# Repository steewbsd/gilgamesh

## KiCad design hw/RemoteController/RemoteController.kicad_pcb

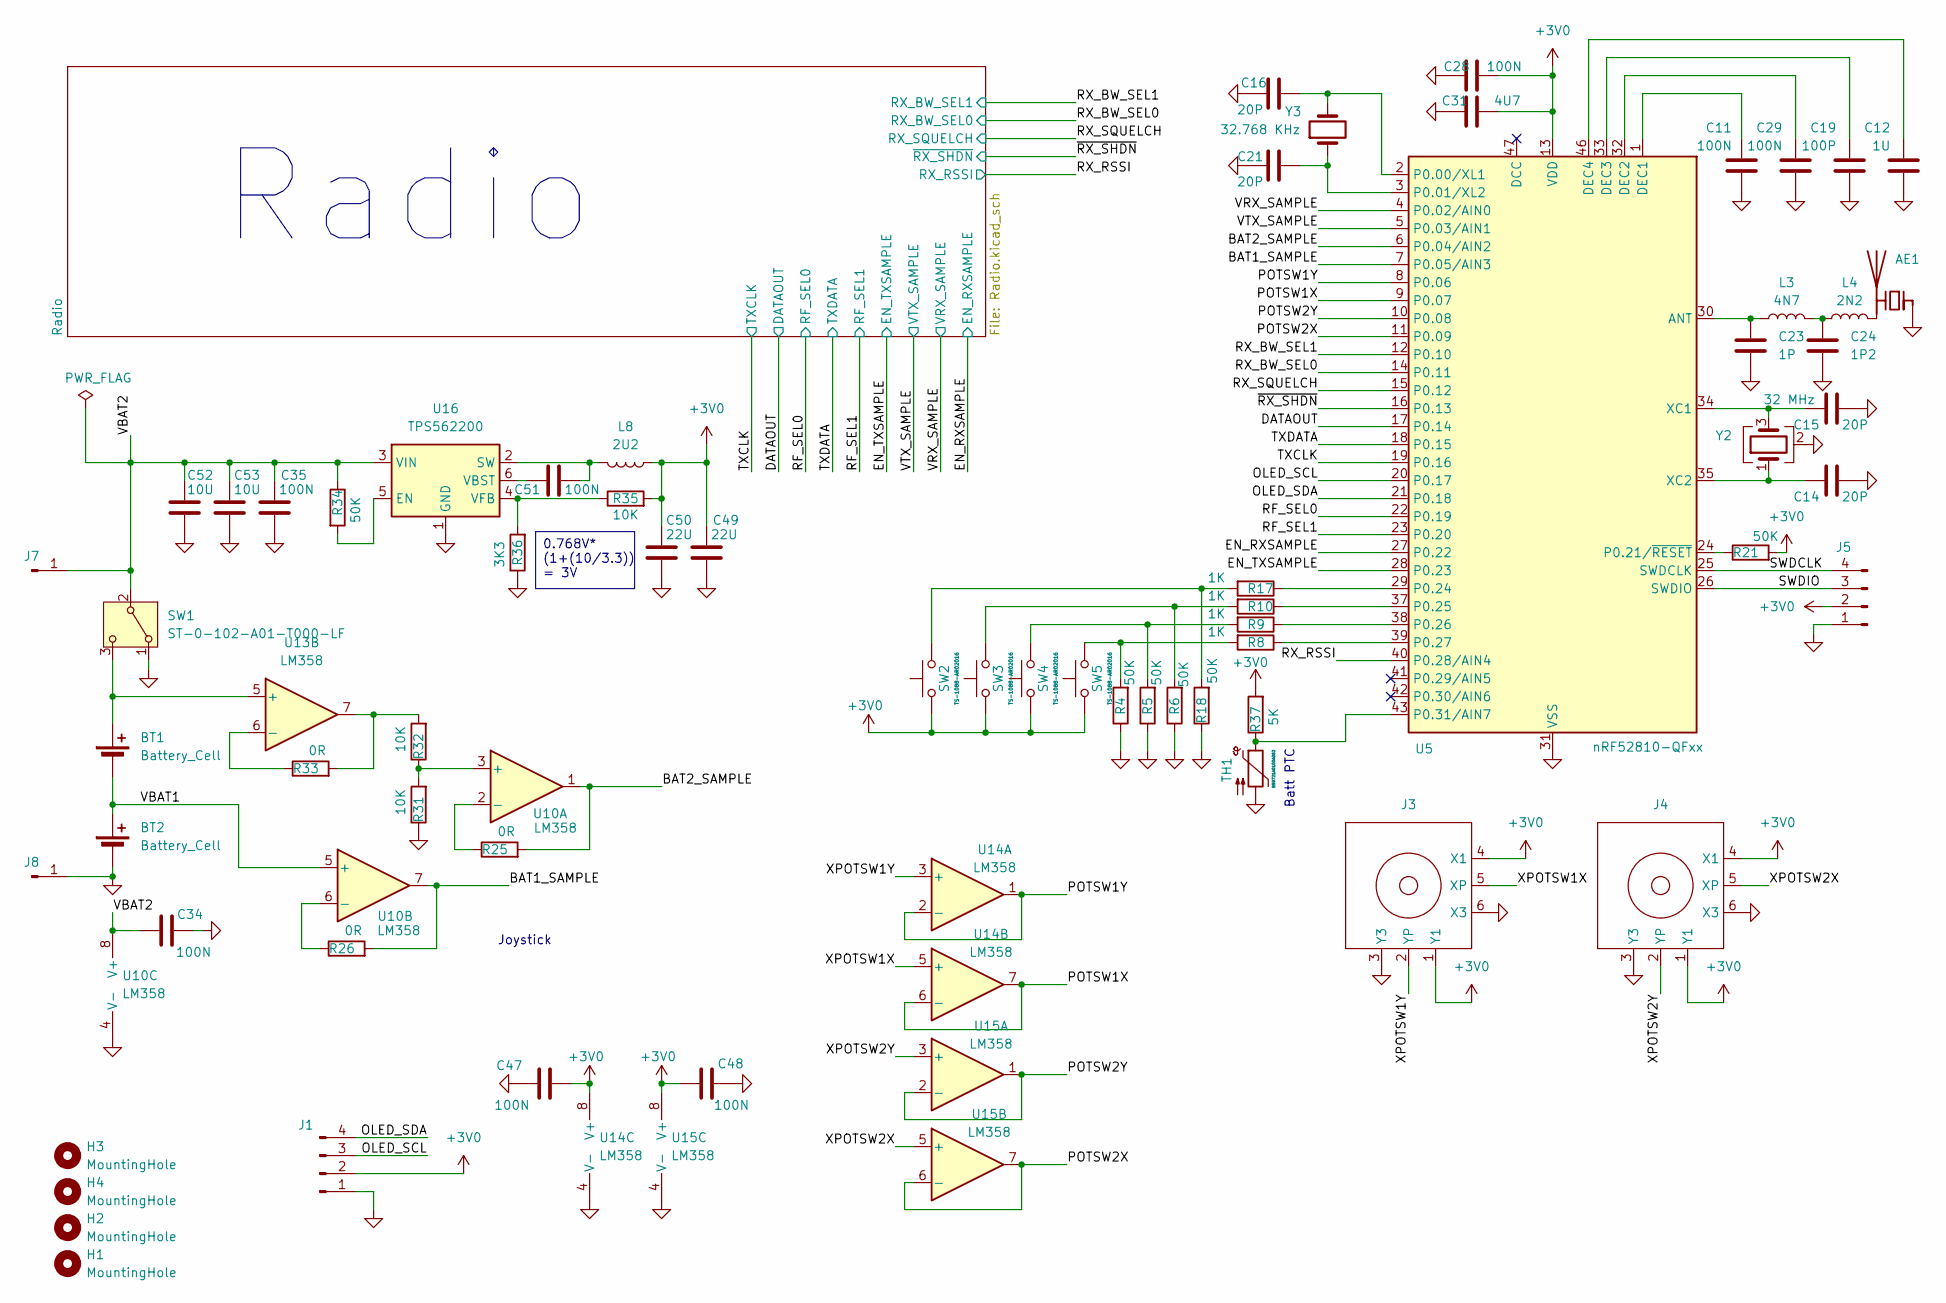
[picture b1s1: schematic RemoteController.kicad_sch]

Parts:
AE1: Antenna_Chip; L_1206_3216Metric_Pad1.22x1.90mm_HandSolder
BT1, BT2: Battery_Cell; BH-AAA-B5BA021
C11, C28, C29, C34, C35, C47, C48, C51: 100N; C_0402_1005Metric_Pad0.74x0.62mm_HandSolder
C12: 1U; C_0402_1005Metric_Pad0.74x0.62mm_HandSolder
C14, C15, C16, C21: 20P; C_0402_1005Metric_Pad0.74x0.62mm_HandSolder
C19: 100P; C_0402_1005Metric_Pad0.74x0.62mm_HandSolder
C23: 1P; C_0402_1005Metric_Pad0.74x0.62mm_HandSolder
C24: 1P2; C_0402_1005Metric_Pad0.74x0.62mm_HandSolder
C31: 4U7; C_0402_1005Metric_Pad0.74x0.62mm_HandSolder
C49, C50: 22U; C_0402_1005Metric_Pad0.74x0.62mm_HandSolder
C52, C53: 10U; C_0402_1005Metric_Pad0.74x0.62mm_HandSolder
H1, H2, H3, H4: MountingHole; MountingHole_2.2mm_M2
J1: Conn_01x04_Pin; PinSocket_1x04_P2.54mm_Horizontal
J3, J4: YG16-FL7.8-B10Ka(80)-R
J5: Conn_01x04_Pin; JST_PH_B4B-PH-K_1x04_P2.00mm_Vertical
J7, J8: Conn_01x01_Pin; PinSocket_1x01_P2.54mm_Vertical
L3: 4N7; L_0603_1608Metric_Pad1.05x0.95mm_HandSolder
L4: 2N2; L_0603_1608Metric_Pad1.05x0.95mm_HandSolder
L8: 2U2; L_0603_1608Metric_Pad1.05x0.95mm_HandSolder
R4, R5, R6, R18, R21, R34: 50K; R_0402_1005Metric_Pad0.72x0.64mm_HandSolder
R8, R9, R10, R17: 1K; R_0402_1005Metric_Pad0.72x0.64mm_HandSolder
R25, R26, R33: 0R; R_0402_1005Metric_Pad0.72x0.64mm_HandSolder
R31, R32, R35: 10K; R_0402_1005Metric_Pad0.72x0.64mm_HandSolder
R36: 3K3; R_0402_1005Metric_Pad0.72x0.64mm_HandSolder
R37: 5K; R_0402_1005Metric_Pad0.72x0.64mm_HandSolder
SW1: ST-0-102-A01-T000-LF; SW_Slide-03_Wuerth-WS-SLTV_10x2.5x6.4_P2.54mm
SW2, SW3, SW4, SW5: TS-1088-AR02016; SW_SPST_TS-1088-xR020
TH1: B59721A0100A062; R_0805_2012Metric_Pad1.20x1.40mm_HandSolder
U5: nRF52810-QFxx; QFN-48-1EP_6x6mm_P0.4mm_EP4.2x4.2mm
U10, U13, U14, U15: LM358; SOIC-8_3.9x4.9mm_P1.27mm
U16: TPS562200; SOT-23-6
Y2: 32 MHz; Crystal_SMD_3225-4Pin_3.2x2.5mm_HandSoldering
Y3: 32.768 KHz; Crystal_SMD_3215-2Pin_3.2x1.5mm

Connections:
+3V0: C28.1, C31.1, C47.2, C48.1, C49.1, C50.1, J1.2, J3.1 (Y1), J3.4 (X1), J4.1 (Y1), J4.4 (X1), J5.2, L8.2, R21.2, R35.2, R37.2, SW2.1, SW3.1, SW4.1, SW5.1, U5.13 (VDD), U5.36 (VDD), U5.48 (VDD), U14.8 (V+), U15.8 (V+); also elsewhere on the board
/BAT1_SAMPLE: R26.2, U5.7 (P0.05/AIN3), U10.7
/BAT2_SAMPLE: R25.2, U5.6 (P0.04/AIN2), U10.1
/DATAOUT: U5.17 (P0.14); also elsewhere on the board
/EN_RXSAMPLE: U5.27 (P0.22); also elsewhere on the board
/EN_TXSAMPLE: U5.28 (P0.23); also elsewhere on the board
/OLED_SCL: J1.3, U5.20 (P0.17)
/OLED_SDA: J1.4, U5.21 (P0.18)
/POTSW1X: U5.9 (P0.07), U14.6 (-), U14.7
/POTSW1Y: U5.8 (P0.06), U14.1, U14.2 (-)
/POTSW2X: U5.11 (P0.09), U15.6 (-), U15.7
/POTSW2Y: U5.10 (P0.08), U15.1, U15.2 (-)
/RF_SEL0: U5.22 (P0.19); also elsewhere on the board
/RF_SEL1: U5.23 (P0.20); also elsewhere on the board
/RX_BW_SEL0: U5.14 (P0.11); also elsewhere on the board
/RX_BW_SEL1: U5.12 (P0.10); also elsewhere on the board
/RX_RSSI: U5.40 (P0.28/AIN4); also elsewhere on the board
/RX_SQUELCH: U5.15 (P0.12); also elsewhere on the board
/SWDCLK: J5.4, U5.25 (SWDCLK)
/SWDIO: J5.3, U5.26 (SWDIO)
/TXCLK: U5.19 (P0.16); also elsewhere on the board
/TXDATA: U5.18 (P0.15); also elsewhere on the board
/VBAT1: BT1.2 (-), BT2.1 (+), U10.5 (+)
/VBAT2: C34.1, C35.1, C52.1, C53.1, J7.1 (Pin_1_1), R34.1, SW1.2 (B), U10.8 (V+), U16.3 (VIN)
/VRX_SAMPLE: U5.4 (P0.02/AIN0); also elsewhere on the board
/VTX_SAMPLE: U5.5 (P0.03/AIN1); also elsewhere on the board
/XPOTSW1X: J3.5 (XP), U14.5 (+)
/XPOTSW1Y: J3.2 (YP), U14.3 (+)
/XPOTSW2X: J4.5 (XP), U15.5 (+)
/XPOTSW2Y: J4.2 (YP), U15.3 (+)
/~RX_SHDN: U5.16 (P0.13); also elsewhere on the board
GND: AE1.1 (FEED), BT2.2 (-), C11.2, C12.2, C14.2, C15.2, C16.2, C19.2, C21.2, C23.2, C24.2, C28.2, C29.2, C31.2, C34.2, C35.2, C47.1, C48.2, C49.2, C50.2, C52.2, C53.2, J1.1, J3.3 (Y3), J3.6 (X3), J4.3 (Y3), J4.6 (X3), J5.1, J8.1 (Pin_1_1), R4.1, R5.1, R6.1, R18.1, R31.1, R36.1, SW1.1 (A), TH1.2, U5.31 (VSS), U5.45 (VSS), U5.49 (VSS), U10.4 (V-), U14.4 (V-), U15.4 (V-), U16.1 (GND), Y2.2 (G), Y2.4 (G); also elsewhere on the board
unnamed: AE1.2 (PCB_Trace), L4.2
unnamed: BT1.1 (+), SW1.3 (C), U13.5 (+)
unnamed: C24.1, L3.2, L4.1
unnamed: R4.2, R8.2, SW5.2
unnamed: R5.2, R9.2, SW4.2
unnamed: R6.2, R10.2, SW3.2
unnamed: R17.2, R18.2, SW2.2
unnamed: R32.2, R33.2, U13.7
unnamed: C23.1, L3.1, U5.30 (ANT)
unnamed: C11.1, U5.1 (DEC1)
unnamed: C29.1, U5.32 (DEC2)
unnamed: C19.1, U5.33 (DEC3)
unnamed: C12.1, U5.46 (DEC4)
unnamed: C16.1, U5.2 (P0.00/XL1), Y3.2
unnamed: C21.1, U5.3 (P0.01/XL2), Y3.1
unnamed: R21.1, U5.24 (P0.21/~RESET)
unnamed: R17.1, U5.29 (P0.24)
unnamed: R10.1, U5.37 (P0.25)
unnamed: R9.1, U5.38 (P0.26)
unnamed: R8.1, U5.39 (P0.27)
unnamed: R37.1, TH1.1, U5.43 (P0.31/AIN7)
unnamed: C15.1, U5.34 (XC1), Y2.3
unnamed: C14.1, U5.35 (XC2), Y2.1
unnamed: R31.2, R32.1, U10.3 (+)
unnamed: R25.1, U10.2 (-)
unnamed: R26.1, U10.6 (-)
unnamed: R33.1, U13.6 (-)
unnamed: R34.2, U16.5 (EN)
unnamed: C51.2, L8.1, U16.2 (SW)
unnamed: C51.1, U16.6 (VBST)
unnamed: R35.1, R36.2, U16.4 (VFB)

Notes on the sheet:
Batt PTC
Joystick
Radio
0.768V* (1+(10/3.3)) = 3V

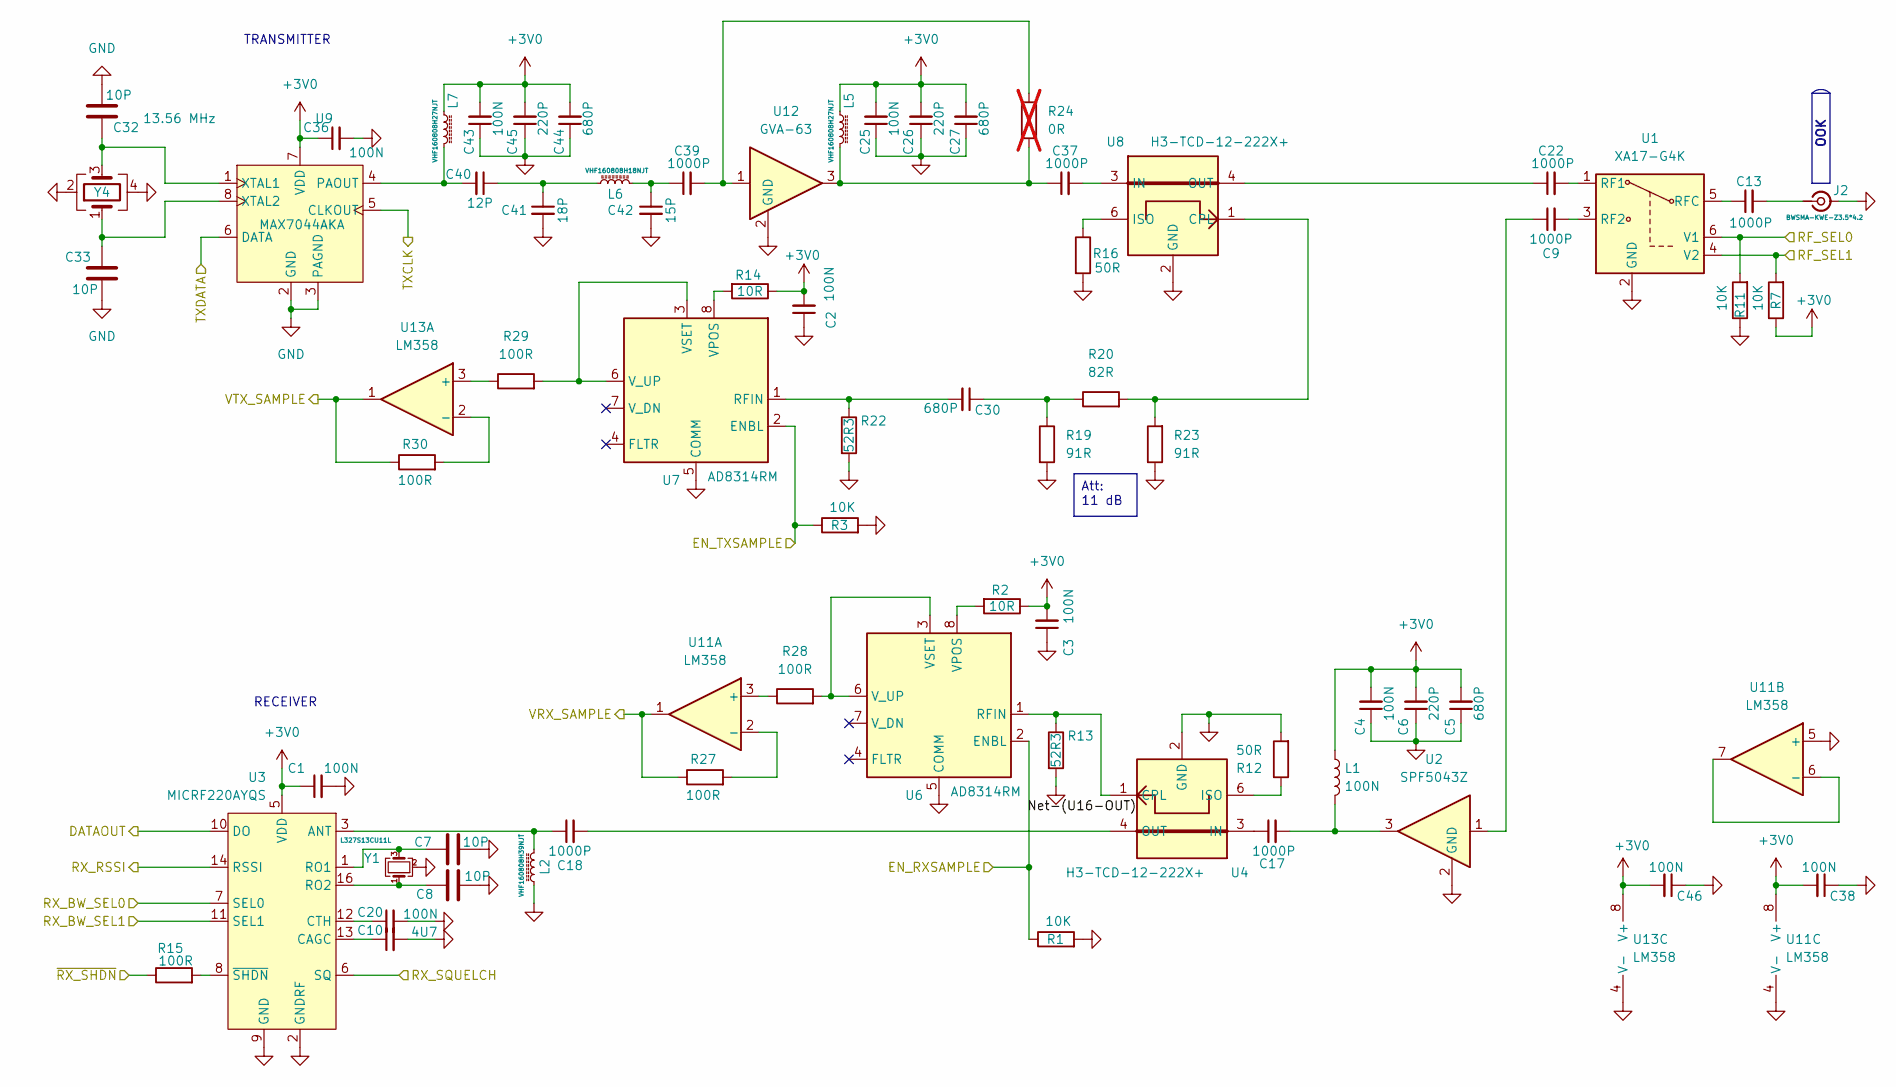
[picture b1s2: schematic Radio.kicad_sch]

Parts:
C1, C2, C3, C4, C20, C25, C36, C38, C43, C46: 100N; C_0402_1005Metric_Pad0.74x0.62mm_HandSolder
C5, C27, C30, C44: 680P; C_0402_1005Metric_Pad0.74x0.62mm_HandSolder
C6, C26, C45: 220P; C_0402_1005Metric_Pad0.74x0.62mm_HandSolder
C7, C8, C32, C33: 10P; C_0402_1005Metric_Pad0.74x0.62mm_HandSolder
C9, C13, C17, C18, C22, C37, C39: 1000P; C_0402_1005Metric_Pad0.74x0.62mm_HandSolder
C10: 4U7; C_0402_1005Metric_Pad0.74x0.62mm_HandSolder
C40: 12P; C_0402_1005Metric_Pad0.74x0.62mm_HandSolder
C41: 18P; C_0402_1005Metric_Pad0.74x0.62mm_HandSolder
C42: 15P; C_0402_1005Metric_Pad0.74x0.62mm_HandSolder
J2: BWSMA-KWE-Z3.5*4.2; SMA_BAT_Wireless_BWSMA-KWE-Z001
L1: 100N; L_0603_1608Metric_Pad1.05x0.95mm_HandSolder
L2: VHF160808H39NJT; L_0603_1608Metric_Pad1.05x0.95mm_HandSolder
L5, L7: 27N; L_0603_1608Metric_Pad1.05x0.95mm_HandSolder
L6: VHF160808H18NJT; L_0603_1608Metric_Pad1.05x0.95mm_HandSolder
R1, R3, R7, R11: 10K; R_0402_1005Metric_Pad0.72x0.64mm_HandSolder
R2, R14: 10R; R_0402_1005Metric_Pad0.72x0.64mm_HandSolder
R12, R16: 50R; R_0402_1005Metric_Pad0.72x0.64mm_HandSolder
R13, R22: 52R3; R_0402_1005Metric_Pad0.72x0.64mm_HandSolder
R15, R27, R28, R29, R30: 100R; R_0402_1005Metric_Pad0.72x0.64mm_HandSolder
R19, R23: 91R; R_0402_1005Metric_Pad0.72x0.64mm_HandSolder
R20: 82R; R_0402_1005Metric_Pad0.72x0.64mm_HandSolder
R24: 0R; R_0402_1005Metric_Pad0.72x0.64mm_HandSolder; not fitted
U1: XA17-G4K; SOT-363_SC-70-6
U2: SPF5043Z; SOT-343_SC-70-4
U3: MICRF220AYQS; QSOP-16_3.9x4.9mm_P0.635mm
U4, U8: H3-TCD-12-222X+; Mini-Circuits_DB1627
U6, U7: AD8314RM; MSOP-8_3x3mm_P0.65mm
U9: MAX7044AKA; TSOT-23-8_HandSoldering
U11, U13: LM358; SOIC-8_3.9x4.9mm_P1.27mm
U12: GVA-63; SOT-89-3_Handsoldering
Y1: L327S13CU11L; Crystal_SMD_3225-4Pin_3.2x2.5mm_HandSoldering
Y4: 13.56 MHz; Crystal_SMD_3225-4Pin_3.2x2.5mm_HandSoldering

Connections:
+3V0: C1.1, C2.2, C3.2, C4.2, C5.2, C6.2, C25.2, C26.2, C27.2, C36.1, C38.2, C43.2, C44.2, C45.2, C46.2, L1.1, L5.1, L7.1, R2.1, R7.1, R14.1, U3.5 (VDD), U9.7 (VDD), U11.8 (V+), U13.8 (V+); also elsewhere on the board
/DATAOUT: U3.10 (DO); also elsewhere on the board
/EN_RXSAMPLE: R1.1, U6.2 (ENBL); also elsewhere on the board
/EN_TXSAMPLE: R3.1, U7.2 (ENBL); also elsewhere on the board
/RF_SEL0: R11.2, U1.6 (V1); also elsewhere on the board
/RF_SEL1: R7.2, U1.4 (V2); also elsewhere on the board
/RX_BW_SEL0: U3.7 (SEL0); also elsewhere on the board
/RX_BW_SEL1: U3.11 (SEL1); also elsewhere on the board
/RX_RSSI: U3.14 (RSSI); also elsewhere on the board
/RX_SQUELCH: U3.6 (SQ); also elsewhere on the board
/TXCLK: U9.5 (CLKOUT); also elsewhere on the board
/TXDATA: U9.6 (DATA); also elsewhere on the board
/VRX_SAMPLE: R27.1, U11.1; also elsewhere on the board
/VTX_SAMPLE: R30.1, U13.1; also elsewhere on the board
/~RX_SHDN: R15.1; also elsewhere on the board
GND: C1.2, C2.1, C3.1, C4.1, C5.1, C6.1, C7.1, C8.1, C10.2, C20.2, C25.1, C26.1, C27.1, C32.2, C33.2, C36.2, C38.1, C41.2, C42.2, C43.1, C44.1, C45.1, C46.1, J2.2 (Ext), L2.1, R1.2, R3.2, R11.1, R12.2, R13.2, R16.2, R19.2, R22.2, R23.1, U1.2 (GND), U2.2 (GND), U2.4 (GND), U3.2 (GNDRF), U3.4 (GNDRF), U3.9 (GND), U4.2 (GND), U6.5 (COMM), U7.5 (COMM), U8.2 (GND), U9.2 (GND), U9.3 (PAGND), U11.4 (V-), U11.5 (+), U12.2 (GND_2), U13.4 (V-), Y1.2 (G), Y1.4 (G), Y4.2, Y4.4; also elsewhere on the board
unnamed: C9.1, U2.1
unnamed: C17.2, L1.2, U2.3
unnamed: C30.1, R19.1, R20.1
unnamed: C37.1, L5.2, R24.1, U12.3
unnamed: C39.1, C42.1, L6.2
unnamed: C39.2, R24.2, U12.1
unnamed: C40.1, C41.1, L6.1
unnamed: C13.2, J2.1 (In)
unnamed: C22.2, U1.1 (RF1)
unnamed: C9.2, U1.3 (RF2)
unnamed: C13.1, U1.5 (RFC)
unnamed: C18.1, L2.2, U3.3 (ANT)
unnamed: C10.1, U3.13 (CAGC)
unnamed: C20.1, U3.12 (CTH)
unnamed: C7.2, U3.1 (RO1), Y1.3
unnamed: C8.2, U3.16 (RO2), Y1.1
unnamed: R15.2, U3.8 (~SHDN)
unnamed: R13.1, U4.1 (CPL), U6.1 (RFIN)
unnamed: C17.1, U4.3 (IN)
unnamed: R12.1, U4.6 (ISO)
unnamed: C18.2, U4.4 (OUT)
unnamed: R2.2, U6.8 (VPOS)
unnamed: R28.2, U6.3 (VSET), U6.6 (V_UP)
unnamed: C30.2, R22.1, U7.1 (RFIN)
unnamed: R14.2, U7.8 (VPOS)
unnamed: R29.2, U7.3 (VSET), U7.6 (V_UP)
unnamed: R20.2, R23.2, U8.1 (CPL)
unnamed: C37.2, U8.3 (IN)
unnamed: R16.1, U8.6 (ISO)
unnamed: C22.1, U8.4 (OUT)
unnamed: C40.2, L7.2, U9.4 (PAOUT)
unnamed: C32.1, U9.1 (XTAL1), Y4.3
unnamed: C33.1, U9.8 (XTAL2), Y4.1
unnamed: R28.1, U11.3 (+)
unnamed: R27.2, U11.2 (-)
unnamed: U11.6 (-), U11.7
unnamed: R29.1, U13.3 (+)
unnamed: R30.2, U13.2 (-)

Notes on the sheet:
RECEIVER
TRANSMITTER
OOK
Att: 11 dB

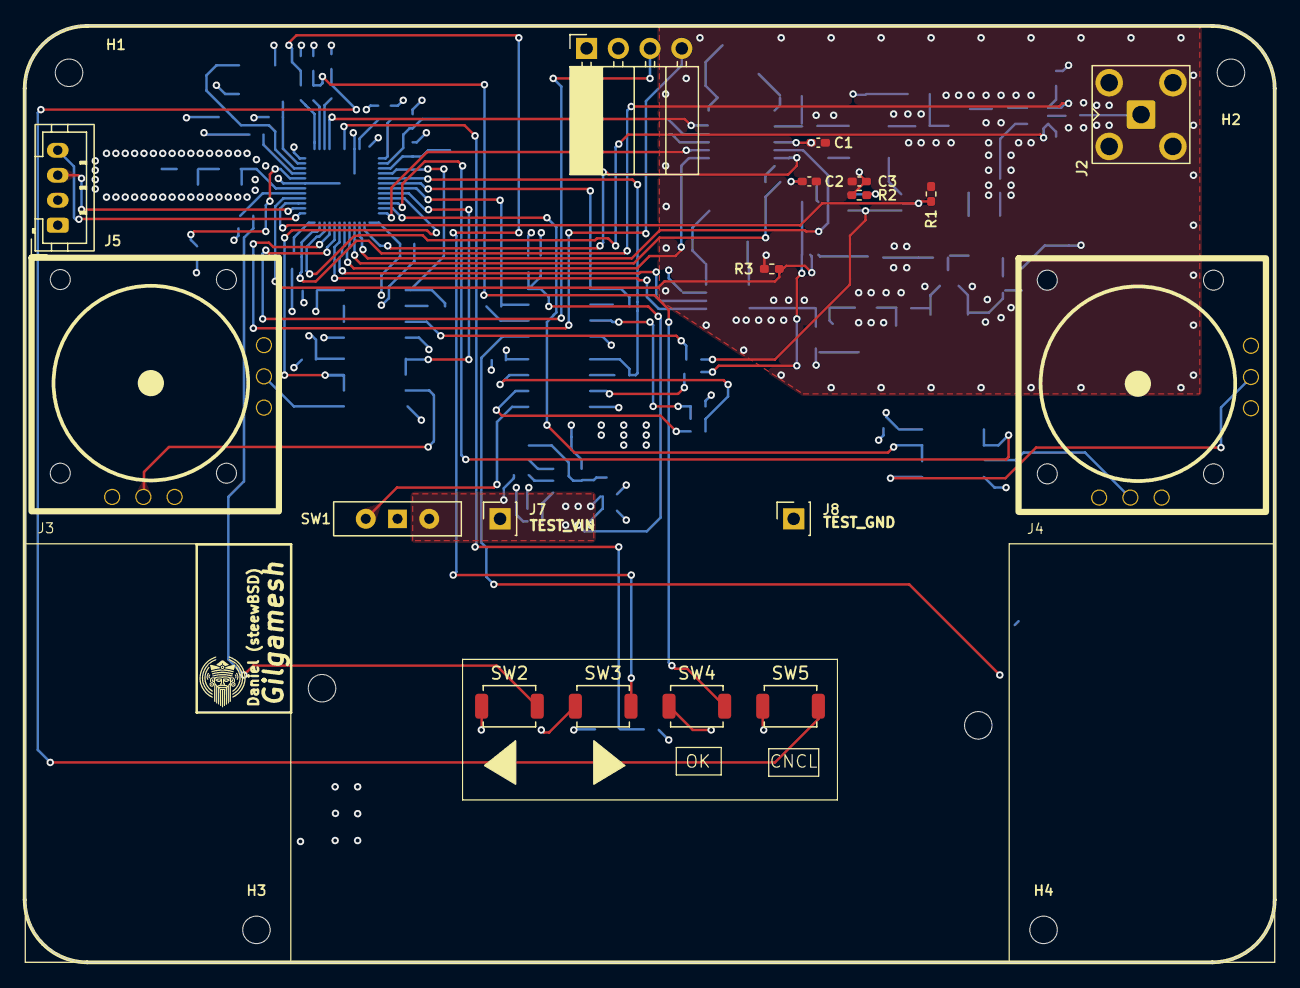
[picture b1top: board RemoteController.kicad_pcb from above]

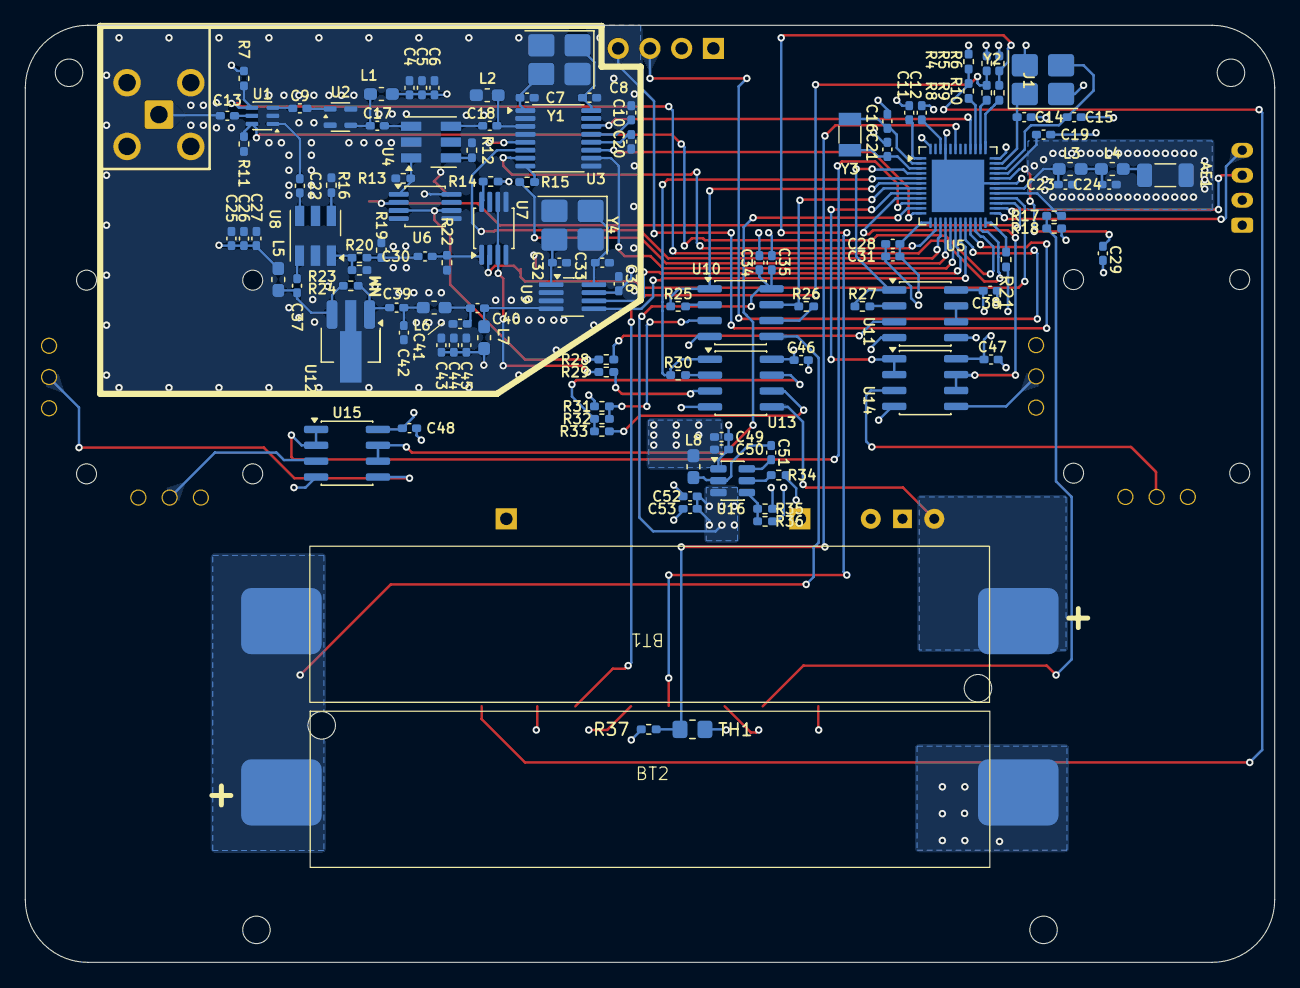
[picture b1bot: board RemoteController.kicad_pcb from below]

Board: 4 copper layers, 100.0 x 75.0 mm, 138 parts (116 on the bottom side), 101 nets.

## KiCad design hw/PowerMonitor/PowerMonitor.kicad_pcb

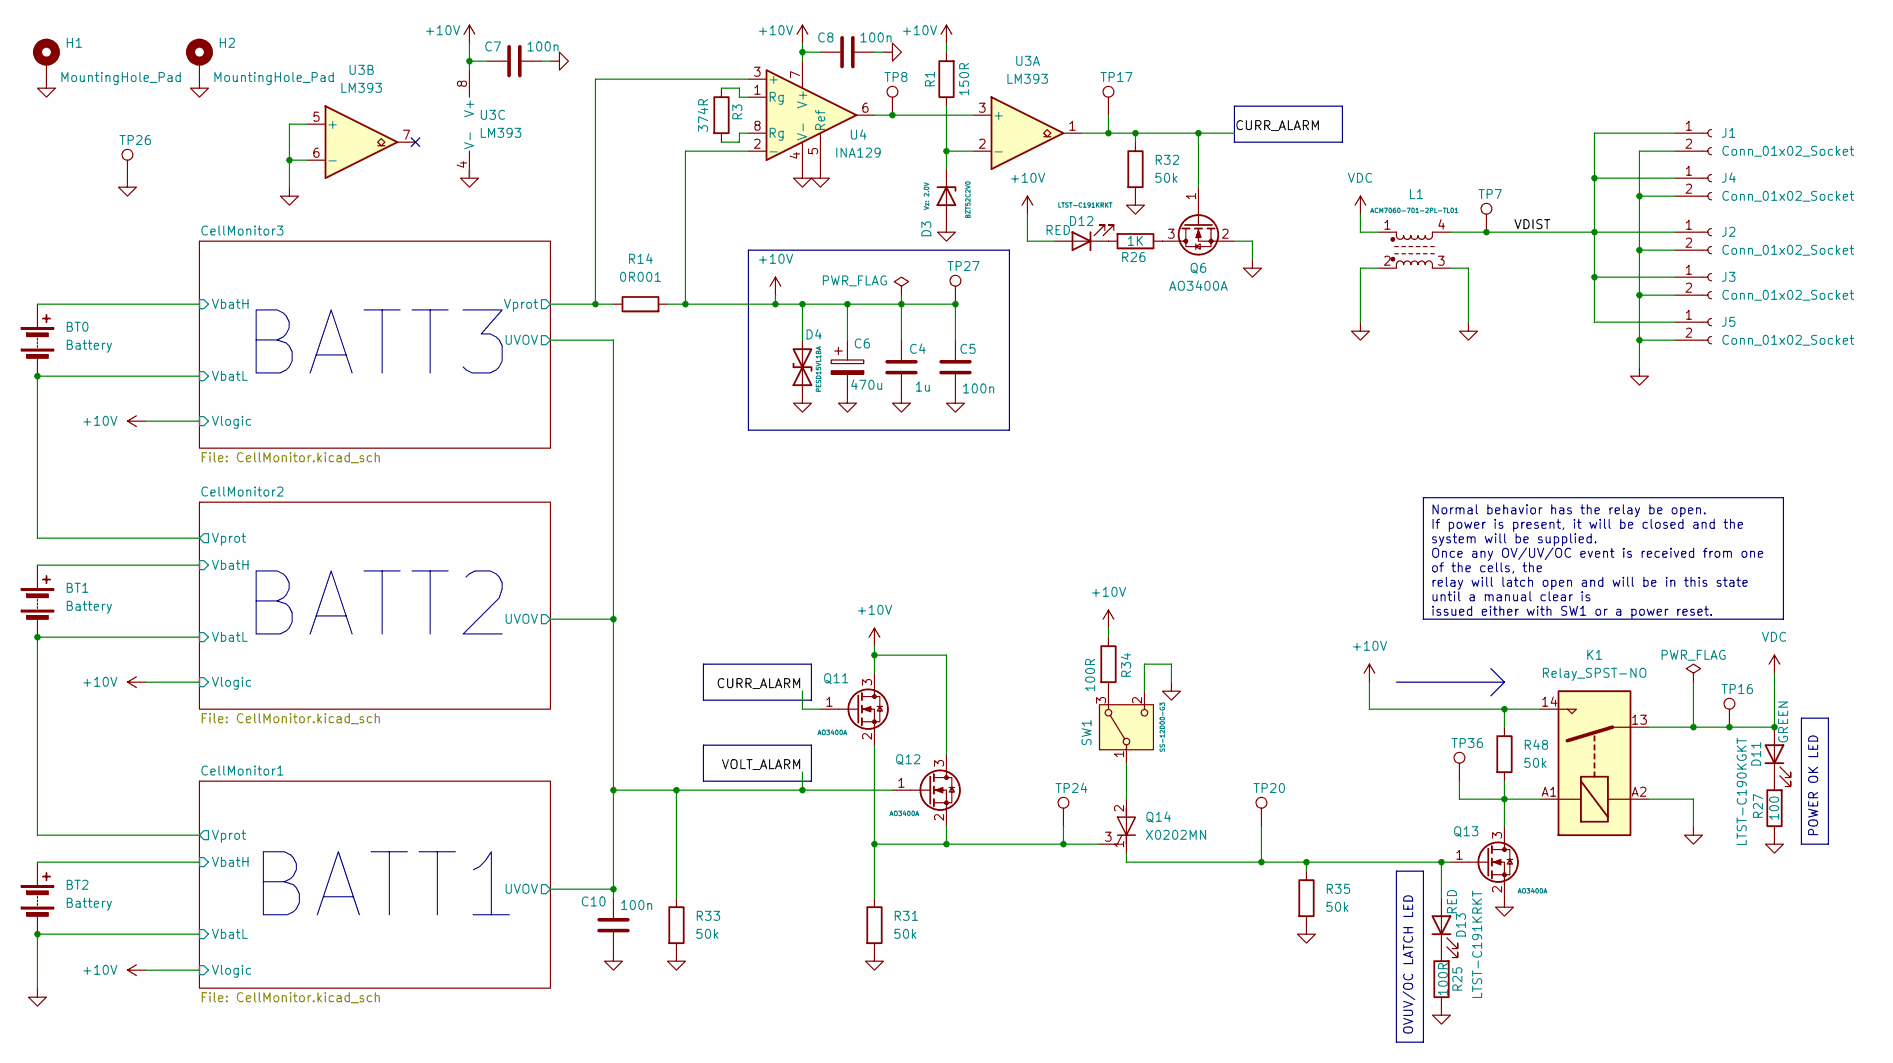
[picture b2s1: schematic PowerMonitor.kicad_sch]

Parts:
BT0, BT1, BT2: Battery; BatteryHolder_Keystone_1042_1x18650
C4: 1u; C_0603_1608Metric_Pad1.08x0.95mm_HandSolder
C5, C7, C8, C10: 100n; C_0603_1608Metric_Pad1.08x0.95mm_HandSolder
C6: 470u; CP_Radial_D8.0mm_P5.00mm
D3: BZT52Bxx; D_SOD-123F
D4: PESD15VL1BA; D_SOD-323_HandSoldering
D11: GREEN; LED_0603_1608Metric
D12, D13: RED; LED_0603_1608Metric
H1, H2: MountingHole_Pad; MountingHole_2.2mm_M2_Pad
J1, J2, J3, J4, J5: Conn_01x02_Socket; JST_VL_B02P-VL_1x02_P6.2mm_Vertical
K1: Relay_SPST-NO; Relay_SPST_Omron_G5NB
L1: L_Ferrite_Coupled_1423; L_CommonModeChoke_TDK_ACM7060
Q6, Q11, Q12, Q13: AO3400A; SOT-23_Handsoldering
Q14: X0202MN; SOT-223
R1: 150R; R_0603_1608Metric_Pad0.98x0.95mm_HandSolder
R3: 374R; R_0603_1608Metric_Pad0.98x0.95mm_HandSolder
R14: 0R001; R_2512_6332Metric_Pad1.40x3.35mm_HandSolder
R25, R34: 100R; R_0603_1608Metric_Pad0.98x0.95mm_HandSolder
R26: 1K; R_0603_1608Metric_Pad0.98x0.95mm_HandSolder
R27: 100; R_0603_1608Metric_Pad0.98x0.95mm_HandSolder
R31, R32, R33, R35, R48: 50k; R_0603_1608Metric_Pad0.98x0.95mm_HandSolder
SW1: SW_Wuerth_450301014042; SW_Slide-03_Wuerth-WS-SLTV_10x2.5x6.4_P2.54mm
TP7, TP8, TP16, TP17, TP20, TP24, TP26, TP27, TP36: TestPoint; TestPoint_Pad_1.0x1.0mm
U3: LM393; SOIC-8_3.9x4.9mm_P1.27mm
U4: INA129; SOIC-8_5.3x6.2mm_P1.27mm

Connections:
+10V: C4.2, C5.2, C6.1, C7.2, C8.2, D4.2 (A2), D12.2 (A), K1.14, Q11.3 (D), Q12.3 (D), R1.2, R14.2, R34.1, R48.1, TP27.1 (1_1), U3.8 (V+), U4.2 (-), U4.7 (V+); also elsewhere on the board
/CURR_ALARM: Q6.1 (G), Q11.1 (G), R32.1, TP17.1 (1_1), U3.1
/CellMonitor1/VbatH: BT2.1 (+); also elsewhere on the board
/CellMonitor1/Vprot: BT1.2 (-); also elsewhere on the board
/CellMonitor2/VbatH: BT1.1 (+); also elsewhere on the board
/CellMonitor2/Vprot: BT0.2 (-); also elsewhere on the board
/CellMonitor3/VbatH: BT0.1 (+); also elsewhere on the board
/CellMonitor3/Vprot: R14.1, U4.3 (+); also elsewhere on the board
/VDIST: J1.1, J2.1, J3.1, J4.1, J5.1, L1.4, TP7.1 (1_1)
/VOLT_ALARM: C10.2, Q12.1 (G), R33.1; also elsewhere on the board
GND: BT2.2 (-), C4.1, C5.1, C6.2, C7.1, C8.1, C10.1, D3.2 (A), D4.1 (A1), H1.1 (1_1), H2.1 (1_1), J1.2, J2.2, J3.2, J4.2, J5.2, K1.A2, L1.2, L1.3, Q6.2 (S), Q13.2 (S), R25.1, R27.1, R31.2, R32.2, R33.2, R35.2, SW1.2 (C), TP26.1 (1_1), U3.4 (V-), U3.5 (+), U3.6 (-), U4.4 (V-), U4.5 (Ref); also elsewhere on the board
unnamed: D3.1 (K), R1.1, U3.2 (-)
unnamed: D11.1 (K), R27.2
unnamed: D12.1 (K), R26.2
unnamed: D13.2 (A), Q13.1 (G), Q14.1 (K), R35.1, TP20.1 (1_1)
unnamed: D13.1 (K), R25.2
unnamed: Q6.3 (D), R26.1
unnamed: Q11.2 (S), Q12.2 (S), Q14.3 (G), R31.1, TP24.1 (1_1)
unnamed: K1.A1, Q13.3 (D), R48.2, TP36.1 (1_1)
unnamed: R3.1, U4.1 (Rg)
unnamed: R3.2, U4.8 (Rg)
unnamed: R34.2, SW1.3 (A)
unnamed: Q14.2 (A), Q14.4 (A), SW1.1 (B)
unnamed: TP8.1 (1_1), U3.3 (+), U4.6
VDC: D11.2 (A), K1.13, L1.1, TP16.1 (1_1)

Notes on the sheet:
BATT1
BATT2
BATT3
POWER OK LED
Normal behavior has the relay be open. If power is present, it will be closed and the system will be supplied. Once any OV/UV/OC event is received from one of the cells, the relay will latch open and will be in this state until a manual clear is issued either with SW1 or a power reset.
OVUV/OC LATCH LED

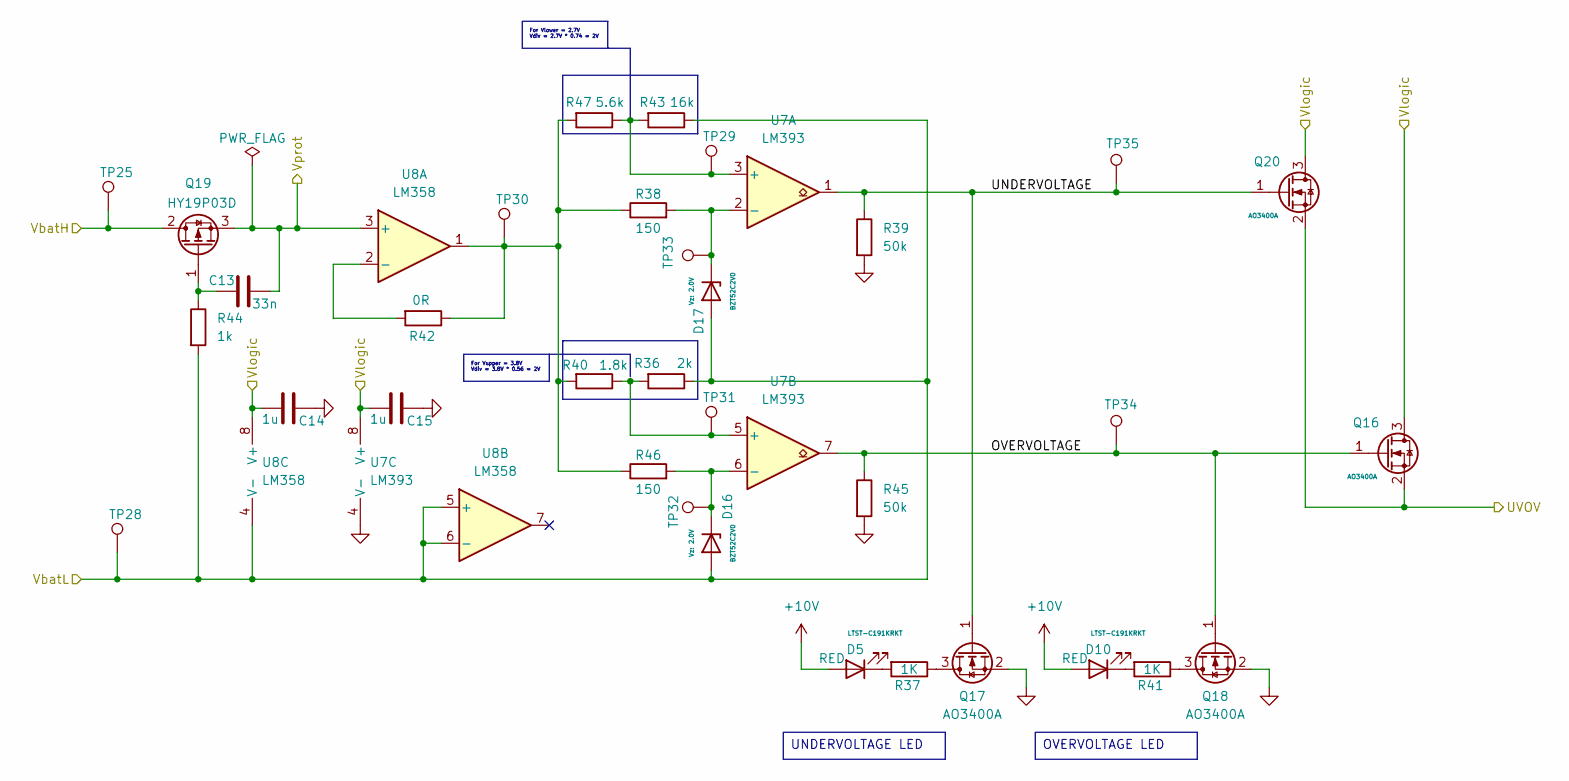
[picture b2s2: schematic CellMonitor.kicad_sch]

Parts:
C13: 33n; C_0603_1608Metric_Pad1.08x0.95mm_HandSolder
C14, C15: 1u; C_0603_1608Metric_Pad1.08x0.95mm_HandSolder
D5, D10: RED; LED_0603_1608Metric
D16, D17: BZT52Bxx; D_SOD-123F
Q16, Q17, Q18, Q20: AO3400A; SOT-23_Handsoldering
Q19: Q_PMOS_GDS; TO-252-2
R36: 2k; R_0603_1608Metric_Pad0.98x0.95mm_HandSolder
R37, R41: 1K; R_0603_1608Metric_Pad0.98x0.95mm_HandSolder
R38, R46: 150; R_0603_1608Metric_Pad0.98x0.95mm_HandSolder
R39, R45: 50k; R_0603_1608Metric_Pad0.98x0.95mm_HandSolder
R40: 1.8k; R_0603_1608Metric_Pad0.98x0.95mm_HandSolder
R42: 0R; R_0603_1608Metric_Pad0.98x0.95mm_HandSolder
R43: 16k; R_0603_1608Metric_Pad0.98x0.95mm_HandSolder
R44: 1k; R_0603_1608Metric_Pad0.98x0.95mm_HandSolder
R47: 5.6k; R_0603_1608Metric_Pad0.98x0.95mm_HandSolder
TP25, TP28, TP29, TP30, TP31, TP32, TP33, TP34, TP35: TestPoint; TestPoint_Pad_1.0x1.0mm
U7: LM393; SOIC-8_3.9x4.9mm_P1.27mm
U8: LM358; SOIC-8_3.9x4.9mm_P1.27mm

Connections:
+10V: C14.2, C15.2, D5.2 (A), D10.2 (A), Q16.3 (D), Q20.3 (D), U7.8 (V+), U8.8 (V+); also elsewhere on the board
/CellMonitor1/OVERVOLTAGE: Q16.1 (G), Q18.1 (G), R45.1, TP34.1 (1_1), U7.7
/CellMonitor1/UNDERVOLTAGE: Q17.1 (G), Q20.1 (G), R39.1, TP35.1 (1_1), U7.1
/CellMonitor1/VbatH: Q19.2 (D), TP25.1 (1_1); also elsewhere on the board
/CellMonitor1/Vprot: C13.2, Q19.3 (S), U8.3 (+); also elsewhere on the board
/VOLT_ALARM: Q16.2 (S), Q20.2 (S); also elsewhere on the board
GND: C14.1, C15.1, D16.2 (A), D17.2 (A), Q17.2 (S), Q18.2 (S), R36.1, R39.2, R43.1, R44.2, R45.2, TP28.1 (1_1), U7.4 (V-), U8.4 (V-), U8.5 (+), U8.6 (-); also elsewhere on the board
unnamed: D5.1 (K), R37.2
unnamed: D10.1 (K), R41.2
unnamed: D16.1 (K), R46.2, TP32.1 (1_1), U7.6 (-)
unnamed: D17.1 (K), R38.2, TP33.1 (1_1), U7.2 (-)
unnamed: Q17.3 (D), R37.1
unnamed: Q18.3 (D), R41.1
unnamed: C13.1, Q19.1 (G), R44.1
unnamed: R38.1, R40.2, R42.1, R46.1, R47.2, TP30.1 (1_1), U8.1
unnamed: R43.2, R47.1, TP29.1 (1_1), U7.3 (+)
unnamed: R36.2, R40.1, TP31.1 (1_1), U7.5 (+)
unnamed: R42.2, U8.2 (-)

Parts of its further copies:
C1, C3, C11, C12: 1u; C_0603_1608Metric_Pad1.08x0.95mm_HandSolder
C2, C9: 33n; C_0603_1608Metric_Pad1.08x0.95mm_HandSolder
D1, D2, D14, D15: BZT52Bxx; D_SOD-123F
D6, D7, D8, D9: RED; LED_0603_1608Metric
Q1, Q2, Q4, Q5, Q7, Q8, Q9, Q10: AO3400A; SOT-23_Handsoldering
Q3, Q15: Q_PMOS_GDS; TO-252-2
R4, R9, R20, R22: 50k; R_0603_1608Metric_Pad0.98x0.95mm_HandSolder
R5, R21: 0R; R_0603_1608Metric_Pad0.98x0.95mm_HandSolder
R6, R24: 1.8k; R_0603_1608Metric_Pad0.98x0.95mm_HandSolder
R7, R29: 1k; R_0603_1608Metric_Pad0.98x0.95mm_HandSolder
R8, R10, R16, R19: 150; R_0603_1608Metric_Pad0.98x0.95mm_HandSolder
R11, R15: 16k; R_0603_1608Metric_Pad0.98x0.95mm_HandSolder
R12, R23: 5.6k; R_0603_1608Metric_Pad0.98x0.95mm_HandSolder
R13, R18, R28, R30: 1K; R_0603_1608Metric_Pad0.98x0.95mm_HandSolder
R17: 2k; R_0603_1608Metric_Pad0.98x0.95mm_HandSolder
TP1, TP2, TP3, TP4, TP5, TP6, TP9, TP10, TP11, TP12, TP13, TP14, TP15, TP18, TP19, TP21, TP22, TP23: TestPoint; TestPoint_Pad_1.0x1.0mm
U1, U6: LM393; SOIC-8_3.9x4.9mm_P1.27mm
U2, U5: LM358; SOIC-8_3.9x4.9mm_P1.27mm

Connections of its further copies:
+10V: C1.2, C3.2, C11.2, C12.2, D6.2 (A), D7.2 (A), D8.2 (A), D9.2 (A), Q4.3 (D), Q5.3 (D), Q7.3 (D), Q10.3 (D), U1.8 (V+), U2.8 (V+), U5.8 (V+), U6.8 (V+); also elsewhere on the board
/CellMonitor1/Vprot: D14.2 (A), D15.2 (A), R15.1, R17.1, R29.2, TP12.1 (1_1), U5.4 (V-), U5.5 (+), U5.6 (-); also elsewhere on the board
/CellMonitor2/OVERVOLTAGE: Q8.1 (G), Q10.1 (G), R22.1, TP19.1 (1_1), U6.7
/CellMonitor2/UNDERVOLTAGE: Q7.1 (G), Q9.1 (G), R20.1, TP15.1 (1_1), U6.1
/CellMonitor2/VbatH: Q15.2 (D), TP21.1 (1_1); also elsewhere on the board
/CellMonitor2/Vprot: C9.2, D1.2 (A), D2.2 (A), Q15.3 (S), R7.2, R11.1, TP23.1 (1_1), U2.4 (V-), U2.5 (+), U2.6 (-), U5.3 (+); also elsewhere on the board
/CellMonitor3/OVERVOLTAGE: Q1.1 (G), Q5.1 (G), R9.1, TP10.1 (1_1), U1.7
/CellMonitor3/UNDERVOLTAGE: Q2.1 (G), Q4.1 (G), R4.1, TP4.1 (1_1), U1.1
/CellMonitor3/VbatH: Q3.2 (D), TP1.1 (1_1); also elsewhere on the board
/CellMonitor3/Vprot: C2.2, Q3.3 (S), U2.3 (+); also elsewhere on the board
/VOLT_ALARM: Q4.2 (S), Q5.2 (S), Q7.2 (S), Q10.2 (S); also elsewhere on the board
GND: C1.1, C3.1, C11.1, C12.1, Q1.2 (S), Q2.2 (S), Q8.2 (S), Q9.2 (S), R4.2, R9.2, R20.2, R22.2, U1.4 (V-), U6.4 (V-); also elsewhere on the board
unnamed: D1.1 (K), R10.2, TP6.1 (1_1), U1.6 (-)
unnamed: D2.1 (K), R8.2, TP2.1 (1_1), U1.2 (-)
unnamed: D6.1 (K), R13.2
unnamed: D7.1 (K), R28.2
unnamed: D8.1 (K), R30.2
unnamed: D9.1 (K), R18.2
unnamed: D14.1 (K), R19.2, TP22.1 (1_1), U6.6 (-)
unnamed: D15.1 (K), R16.2, TP18.1 (1_1), U6.2 (-)
unnamed: Q1.3 (D), R28.1
unnamed: Q2.3 (D), R13.1
unnamed: C2.1, Q3.1 (G), R7.1
unnamed: Q8.3 (D), R30.1
unnamed: Q9.3 (D), R18.1
unnamed: C9.1, Q15.1 (G), R29.1
unnamed: R5.1, R6.2, R8.1, R10.1, R12.2, TP9.1 (1_1), U2.1
unnamed: R16.1, R19.1, R21.1, R23.2, R24.2, TP11.1 (1_1), U5.1
unnamed: R11.2, R12.1, TP3.1 (1_1), U1.3 (+)
unnamed 54: R6.1, TP5.1 (1_1), U1.5 (+); also elsewhere on the board
unnamed: R5.2, U2.2 (-)
unnamed: R21.2, U5.2 (-)
unnamed: R15.2, R23.1, TP14.1 (1_1), U6.3 (+)
unnamed: R17.2, R24.1, TP13.1 (1_1), U6.5 (+)

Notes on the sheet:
OVERVOLTAGE LED
UNDERVOLTAGE LED
For Vlower = 2.7V Vdiv = 2.7V * 0.74 = 2V
For Vupper = 3.8V Vdiv = 3.8V * 0.56 = 2V
